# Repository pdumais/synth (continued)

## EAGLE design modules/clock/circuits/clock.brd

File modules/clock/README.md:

# Clock module
A rotary encoder connected to the module will set the clock to a BPM from 30 to 240. 
1 square wave output on the CLK pin, and another one, 8 times faster, on the clk8 output.

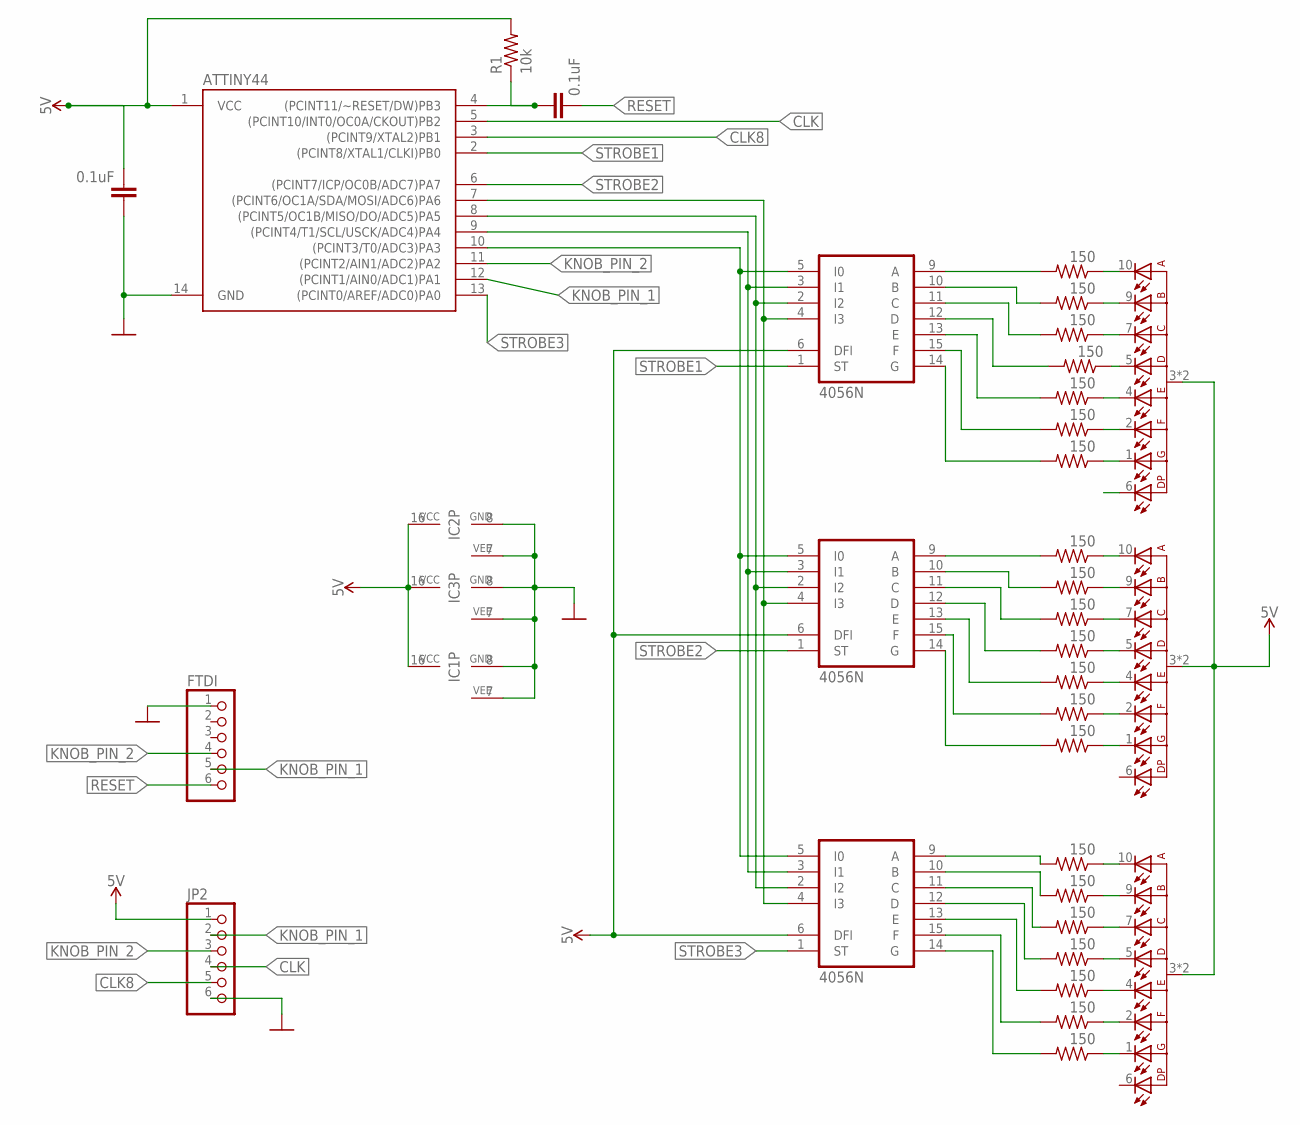
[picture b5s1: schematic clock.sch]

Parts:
ATTINY44: ATTINY84ATTINY84-20PU; DIP14
C2, C3: 0.1uF; CAP-PTH-SMALL-KIT
D1, D2, D3: 157119S12801; WL-T7DS_0.39INCH
FTDI: PINHD-1X6; 1X06
IC1, IC2, IC3: 4056N; DIL16
JP2: PINHD-1X6; 1X06
R1: 10k; 0207/12
R2, R3, R4, R5, R6, R7, R8, R10, R11, R12, R13, R14, R15, R16, R18, R19, R20, R21, R22, R23, R24: 150; 0207/12

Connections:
5V: ATTINY44.1 (VCC), C3.2, D1.3 (+), D1.8 (+), D2.3 (+), D2.8 (+), D3.3 (+), D3.8 (+), IC1.6 (DFI), IC1.16 (VCC), IC2.6 (DFI), IC2.16 (VCC), IC3.6 (DFI), IC3.16 (VCC), JP2.1, R1.2
CLK: ATTINY44.5 ((PCINT10/INT0/OC0A/CKOUT)PB2), JP2.4
CLK8: ATTINY44.3 ((PCINT9/XTAL2)PB1), JP2.5
GND: ATTINY44.14 (GND), C3.1, FTDI.1, IC1.7 (VEE), IC1.8 (GND), IC2.7 (VEE), IC2.8 (GND), IC3.7 (VEE), IC3.8 (GND), JP2.6
KNOB_PIN_1: ATTINY44.12 ((PCINT1/AIN0/ADC1)PA1), FTDI.5, JP2.2
KNOB_PIN_2: ATTINY44.11 ((PCINT2/AIN1/ADC2)PA2), FTDI.4, JP2.3
unnamed: IC1.9 (A), R18.2
unnamed: ATTINY44.4 ((PCINT11/~RESET/DW)PB3), C2.1, R1.1
unnamed: ATTINY44.10 ((PCINT3/T0/ADC3)PA3), IC1.5 (I0), IC2.5 (I0), IC3.5 (I0)
unnamed: IC1.10 (B), R19.2
unnamed: ATTINY44.9 ((PCINT4/T1/SCL/USCK/ADC4)PA4), IC1.3 (I1), IC2.3 (I1), IC3.3 (I1)
unnamed: ATTINY44.8 ((PCINT5/OC1B/MISO/DO/ADC5)PA5), IC1.2 (I2), IC2.2 (I2), IC3.2 (I2)
unnamed: ATTINY44.7 ((PCINT6/OC1A/SDA/MOSI/ADC6)PA6), IC1.4 (I3), IC2.4 (I3), IC3.4 (I3)
unnamed: IC1.11 (C), R20.2
unnamed: IC1.12 (D), R21.2
unnamed: IC1.13 (E), R22.2
unnamed: IC1.15 (F), R23.2
unnamed: IC1.14 (G), R24.2
unnamed: IC3.14 (G), R16.2
unnamed: IC3.15 (F), R15.2
unnamed: IC3.13 (E), R14.2
unnamed: IC3.12 (D), R13.2
unnamed: IC3.11 (C), R12.2
unnamed: IC3.10 (B), R11.2
unnamed: IC3.9 (A), R10.2
unnamed: IC2.14 (G), R8.2
unnamed: IC2.15 (F), R7.2
unnamed: IC2.13 (E), R6.2
unnamed: IC2.12 (D), R5.2
unnamed: IC2.11 (C), R4.2
unnamed: IC2.10 (B), R3.2
unnamed: IC2.9 (A), R2.2
unnamed: D1.10 (7), R2.1
unnamed: D1.9 (6), R3.1
unnamed: D1.7 (4), R4.1
unnamed: D1.5 (2), R5.1
unnamed: D1.4 (1), R6.1
unnamed: D1.2 (9), R7.1
unnamed: D1.1 (10), R8.1
unnamed: D3.10 (7), R10.1
unnamed: D3.9 (6), R11.1
unnamed: D3.7 (4), R12.1
unnamed: D3.5 (2), R13.1
unnamed: D3.4 (1), R14.1
unnamed: D3.2 (9), R15.1
unnamed: D3.1 (10), R16.1
unnamed: D2.10 (7), R18.1
unnamed: D2.9 (6), R19.1
unnamed: D2.7 (4), R20.1
unnamed: D2.5 (2), R21.1
unnamed: D2.4 (1), R22.1
unnamed: D2.2 (9), R23.1
unnamed: D2.1 (10), R24.1
RESET: C2.2, FTDI.6
STROBE1: ATTINY44.2 ((PCINT8/XTAL1/CLKI)PB0), IC2.1 (ST)
STROBE2: ATTINY44.6 ((PCINT7/ICP/OC0B/ADC7)PA7), IC3.1 (ST)
STROBE3: ATTINY44.13 ((PCINT0/AREF/ADC0)PA0), IC1.1 (ST)

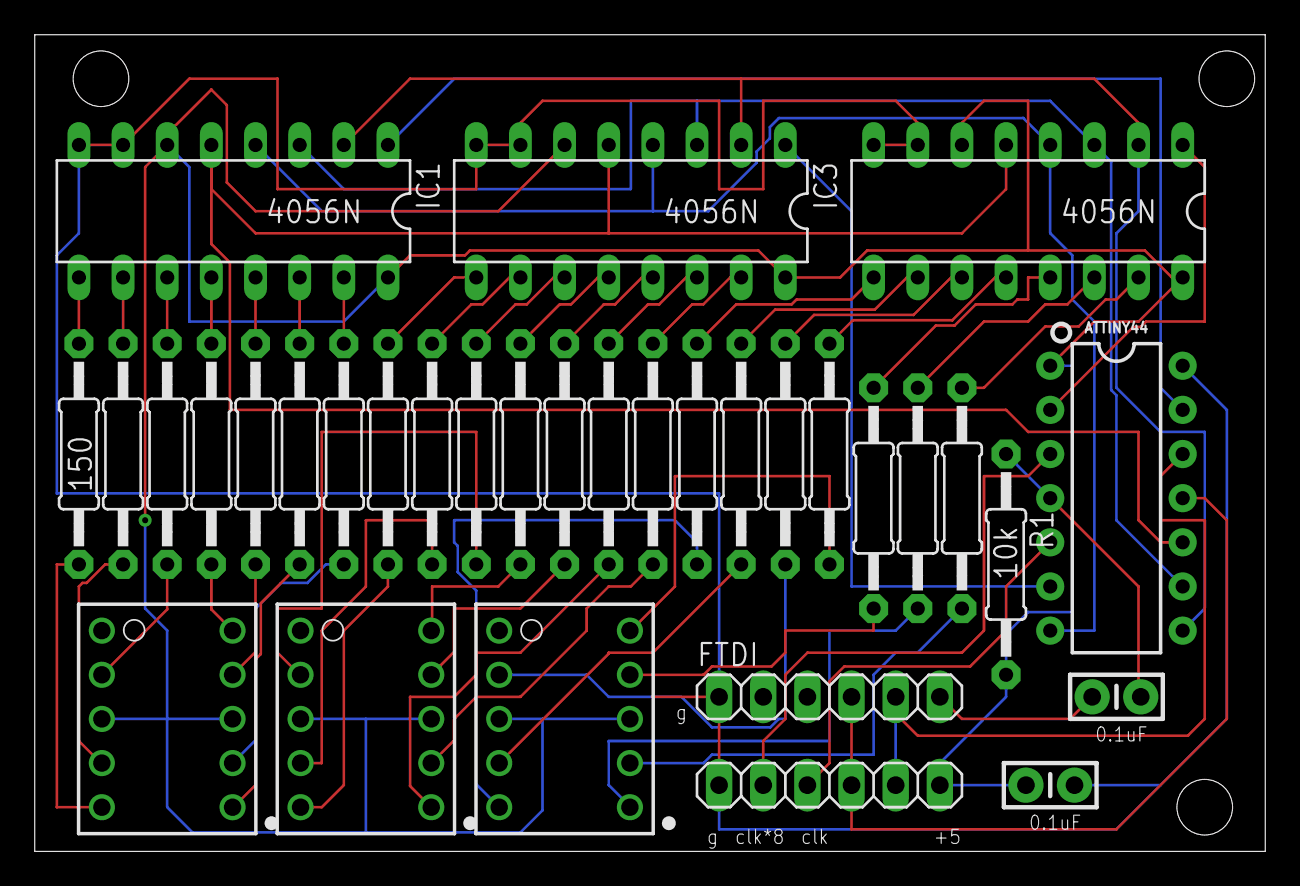
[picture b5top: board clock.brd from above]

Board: 2 copper layers, 70.8 x 47.0 mm, 33 parts (0 on the bottom side), 57 nets.

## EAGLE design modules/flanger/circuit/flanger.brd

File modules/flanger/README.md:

# Flanger
Based on a 2048 stage BBD.

# Design
```mermaid
graph LR;
    Input-->InputMixer;
    InputMixer-->OutputMixer;
    InputMixer-->InLPF;
    InLPF-->BBD;
    BBD-->OutLPF;
    OutLPF-->OutputMixer;  
    OutLPF-->InputMixer;
```

# Inputs
    Analog controls
        Audio In
        LFO CV: input CV to use as external LFO. Will be ignored unless Rate and Depth are both zero
        Dry/Wet: output Mixer
        trimpot: for the BBD outputs balancing

    uC controls
        Rate: To control the speed of the embeded (in the uC) triangle LFO
        Depth: To control the amplitude of the LFO. 
        Offset: Base value on which the LFO will be added 

# Outputs
    Audio Out

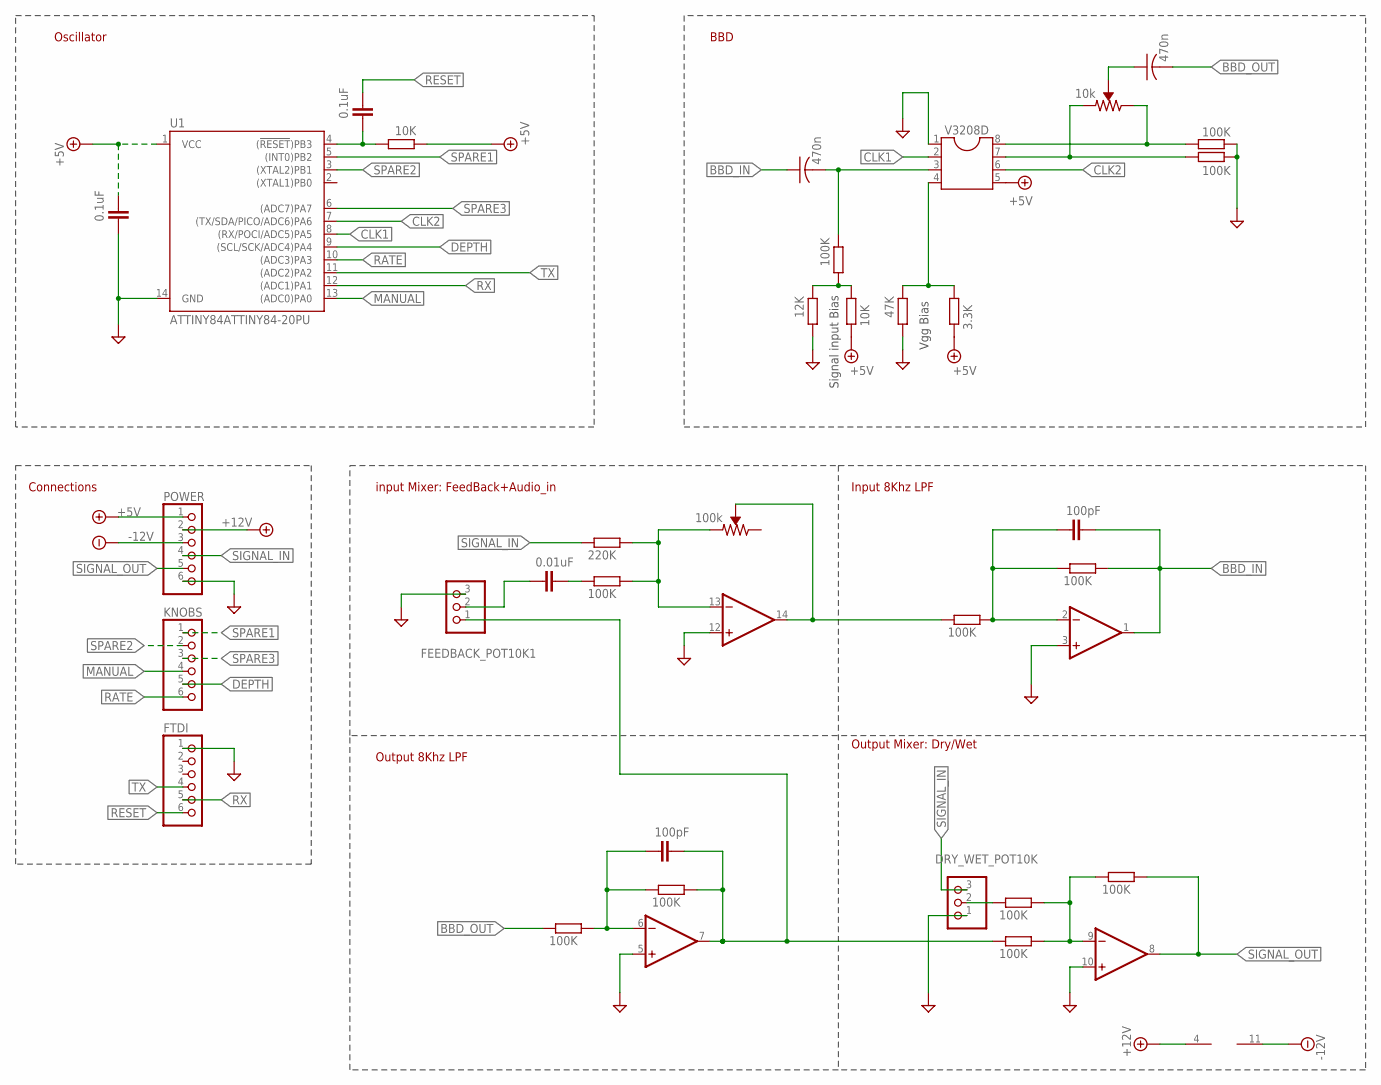
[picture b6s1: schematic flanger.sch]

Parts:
C1, C2: 470n; C050-025X075
C3, C4: 100pF; C5B2.5
C5: 0.01uF; C5B2.5
C6, C7: 0.1uF; C5B2.5
DRY_WET_POT10K: PINHD-1X3; 1X03
FEEDBACK_POT10K1: PINHD-1X3; 1X03
FTDI: PINHD-1X6; 1X06
IC1: LM324N; DIL14
KNOBS: PINHD-1X6; 1X06
POWER: PINHD-1X6; 1X06
R1: 12K; 0207/10
R2, R6, R7, R8, R9, R10, R11, R13, R14, R16, R17: 100K; 0207/10
R3, R18: 10K; 0207/10
R4: 47K; 0207/10
R5: 3.3K; 0207/10
R15: 220K; 0207/10
U1: ATTINY84ATTINY84-20PU; DIP14
V3208D: DIL8; DIL08
VR1: 10k; TRIMPOT-PTH-3386U
VR2: 100k; TRIMPOT-PTH-3386U

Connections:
+5V: C6.2, POWER.1, R3.2, R5.2, R18.2, U1.1 (VCC), V3208D.5
+12V: IC1.4 (V+), POWER.2
-12V: IC1.11 (V-), POWER.3
BBD_IN: C1.1, C3.2, IC1.1 (OUT), R8.2
BBD_OUT: C2.2, R11.1
CLK1: U1.8 ((RX/POCI/ADC5)PA5), V3208D.2
CLK2: U1.7 ((TX/SDA/PICO/ADC6)PA6), V3208D.6
DEPTH: KNOBS.5, U1.9 ((SCL/SCK/ADC4)PA4)
GND: C6.1, DRY_WET_POT10K.1, FEEDBACK_POT10K1.3, FTDI.1, IC1.3 (+IN), IC1.5 (+IN), IC1.10 (+IN), IC1.12 (+IN), POWER.6, R1.1, R4.1, R6.1, R7.1, U1.14 (GND), V3208D.1
MANUAL: KNOBS.4, U1.13 ((ADC0)PA0)
unnamed: R6.2, V3208D.8, VR1.3 (CW)
unnamed: R7.2, V3208D.7, VR1.1 (CCW)
unnamed: C1.2, R2.2, V3208D.3
unnamed: C2.1, VR1.2 (WIPER)
unnamed: R1.2, R2.1, R3.1
unnamed: R4.2, R5.1, V3208D.4
unnamed: IC1.13 (-IN), R15.2, R16.2, VR2.1 (CCW)
unnamed: C3.1, IC1.2 (-IN), R8.1, R9.2
unnamed: C4.1, IC1.6 (-IN), R10.1, R11.2
unnamed: DRY_WET_POT10K.2, R17.1
unnamed: IC1.14 (OUT), R9.1, VR2.2 (WIPER)
unnamed: C4.2, FEEDBACK_POT10K1.1, IC1.7 (OUT), R10.2, R14.1
unnamed: IC1.9 (-IN), R13.1, R14.2, R17.2
unnamed: C5.2, R16.1
unnamed: C5.1, FEEDBACK_POT10K1.2
unnamed: C7.1, R18.1, U1.4 ((!RESET!)PB3)
RATE: KNOBS.6, U1.10 ((ADC3)PA3)
RESET: C7.2, FTDI.6
RX: FTDI.5, U1.12 ((ADC1)PA1)
SIGNAL_IN: DRY_WET_POT10K.3, POWER.4, R15.1
SIGNAL_OUT: IC1.8 (OUT), POWER.5, R13.2
SPARE1: KNOBS.1, U1.5 ((INT0)PB2)
SPARE2: KNOBS.2, U1.3 ((XTAL2)PB1)
SPARE3: KNOBS.3, U1.6 ((ADC7)PA7)
TX: FTDI.4, U1.11 ((ADC2)PA2)

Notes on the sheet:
Vgg Bias
Signal input Bias
Input 8Khz LPF
Output 8Khz LPF
Output Mixer: Dry/Wet
input Mixer: FeedBack+Audio_in
BBD
Oscillator
Connections

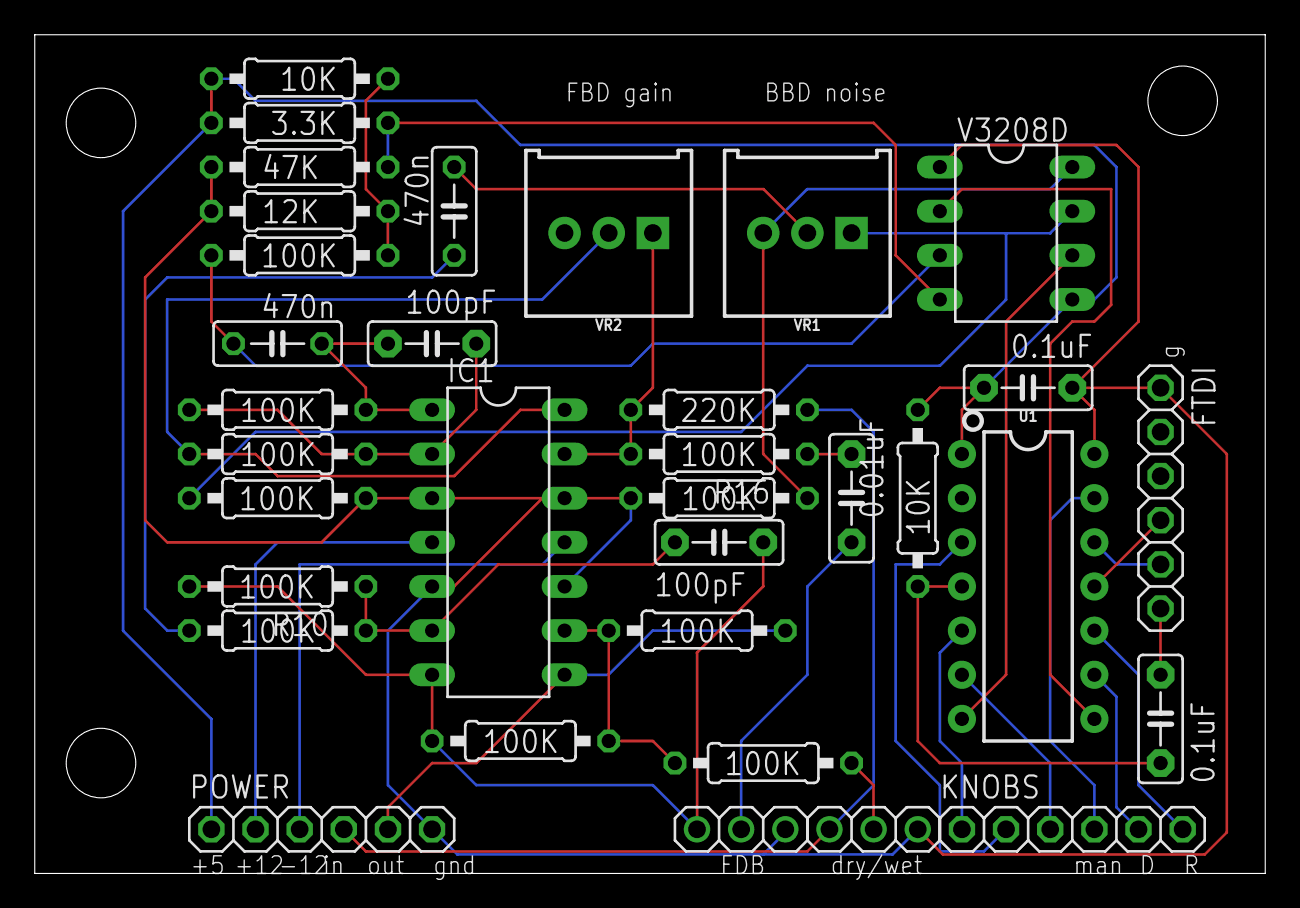
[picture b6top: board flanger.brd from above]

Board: 2 copper layers, 70.8 x 48.2 mm, 34 parts (0 on the bottom side), 35 nets.

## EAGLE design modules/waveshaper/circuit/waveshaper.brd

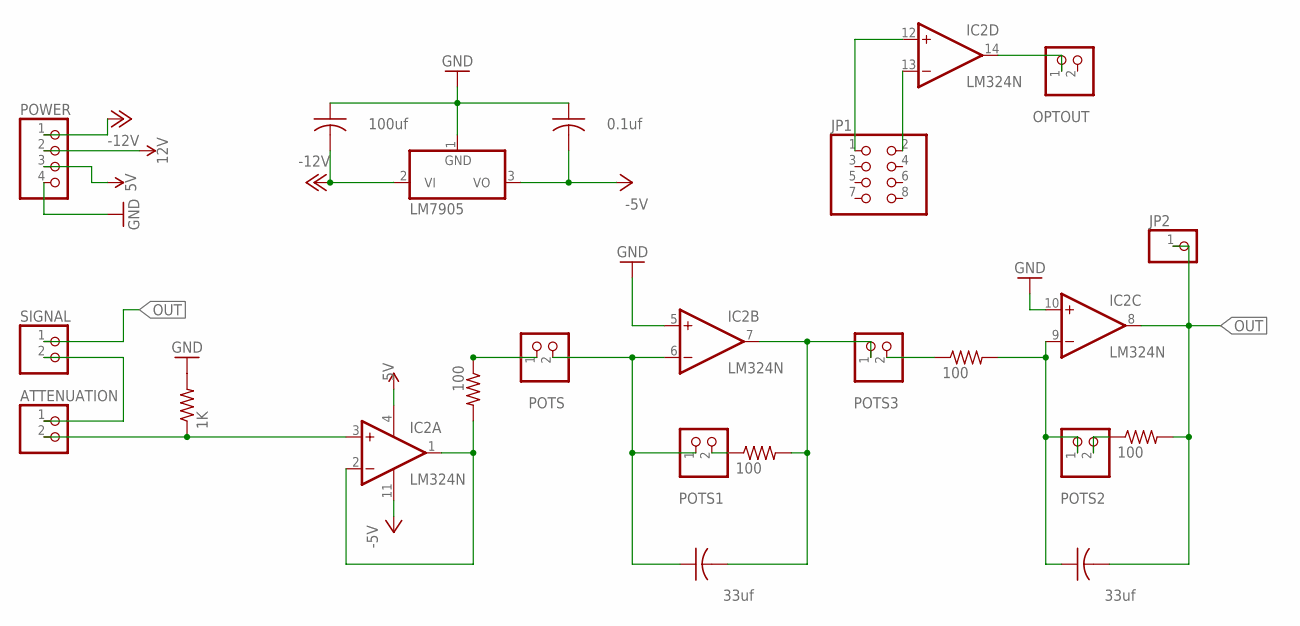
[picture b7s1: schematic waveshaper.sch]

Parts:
ATTENUATION: PINHD-1X2; 1X02
C1: 100uf; C025-024X044
C2: 0.1uf; C025-024X044
C3, C4: 33uf; C025-024X044
IC2: LM324N; DIL14
JP1: PINHD-2X4; 2X04
JP2: PINHD-1X1; 1X01
LM7905: 7905T; TO220H
OPTOUT: PINHD-1X2; 1X02
POTS, POTS1, POTS2, POTS3: PINHD-1X2; 1X02
POWER: PINHD-1X4; 1X04
R1: 1K; 0207/12
R2, R3, R4, R5: 100; 0207/12
SIGNAL: PINHD-1X2; 1X02

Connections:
5V: IC2.4 (V+), POWER.3
12V: POWER.2
-5V: C2.2, IC2.11 (V-), LM7905.3 (VO)
-12V: C1.2, LM7905.2 (VI), POWER.1
GND: C1.1, C2.1, IC2.5 (+IN), IC2.10 (+IN), LM7905.1 (GND), POWER.4, R1.2
IN: ATTENUATION.2, IC2.3 (+IN), R1.1
unnamed: ATTENUATION.1, SIGNAL.2
unnamed: C3.1, IC2.6 (-IN), POTS.2, POTS1.1
unnamed: C3.2, IC2.7 (OUT), POTS3.1, R3.2
unnamed: C4.1, IC2.9 (-IN), POTS2.1, R5.2
unnamed: IC2.14 (OUT), OPTOUT.1
unnamed: IC2.13 (-IN), JP1.2
unnamed: IC2.12 (+IN), JP1.1
unnamed: IC2.1 (OUT), IC2.2 (-IN), R2.2
unnamed: POTS.1, R2.1
unnamed: POTS1.2, R3.1
unnamed: POTS2.2, R4.1
unnamed: POTS3.2, R5.1
OUT: C4.2, IC2.8 (OUT), JP2.1, R4.2, SIGNAL.1

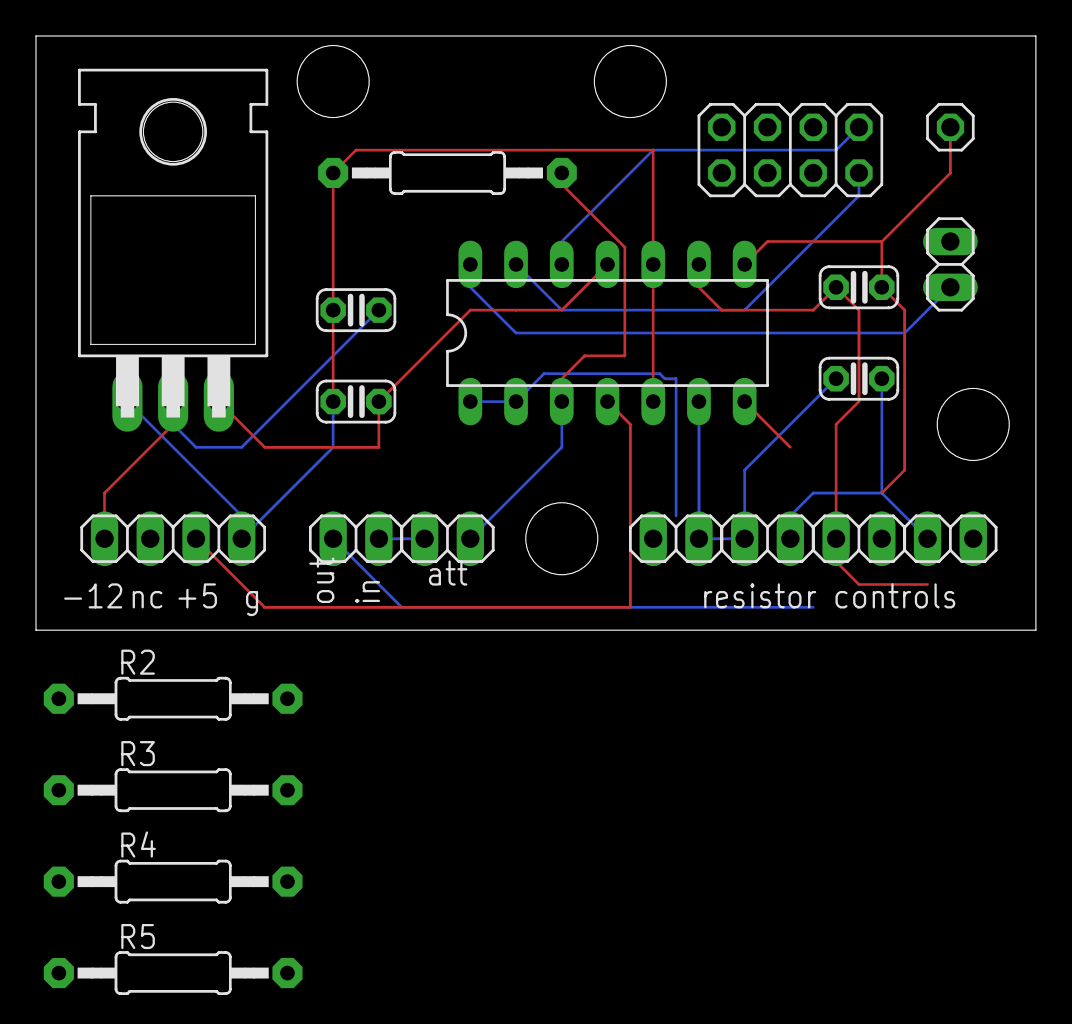
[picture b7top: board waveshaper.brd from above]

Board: 2 copper layers, 55.5 x 33.0 mm, 21 parts (0 on the bottom side), 18 nets.

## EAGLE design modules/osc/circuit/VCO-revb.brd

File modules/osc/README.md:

# Oscillator
- 2 square wave oscillators.
    1 osc as main wave, and 2nd osc used as detune.
- 4 sqaurewave LFOs

# Inputs
- VCO freq
- Detune
- VCO pulse width
- LFO1 freq 
- LFO2 freq 
- LFO3 freq 
- LFO4 freq 

# Outputs
- Audio out
- LFO1
- LFO2
- LFO3
- LFO4

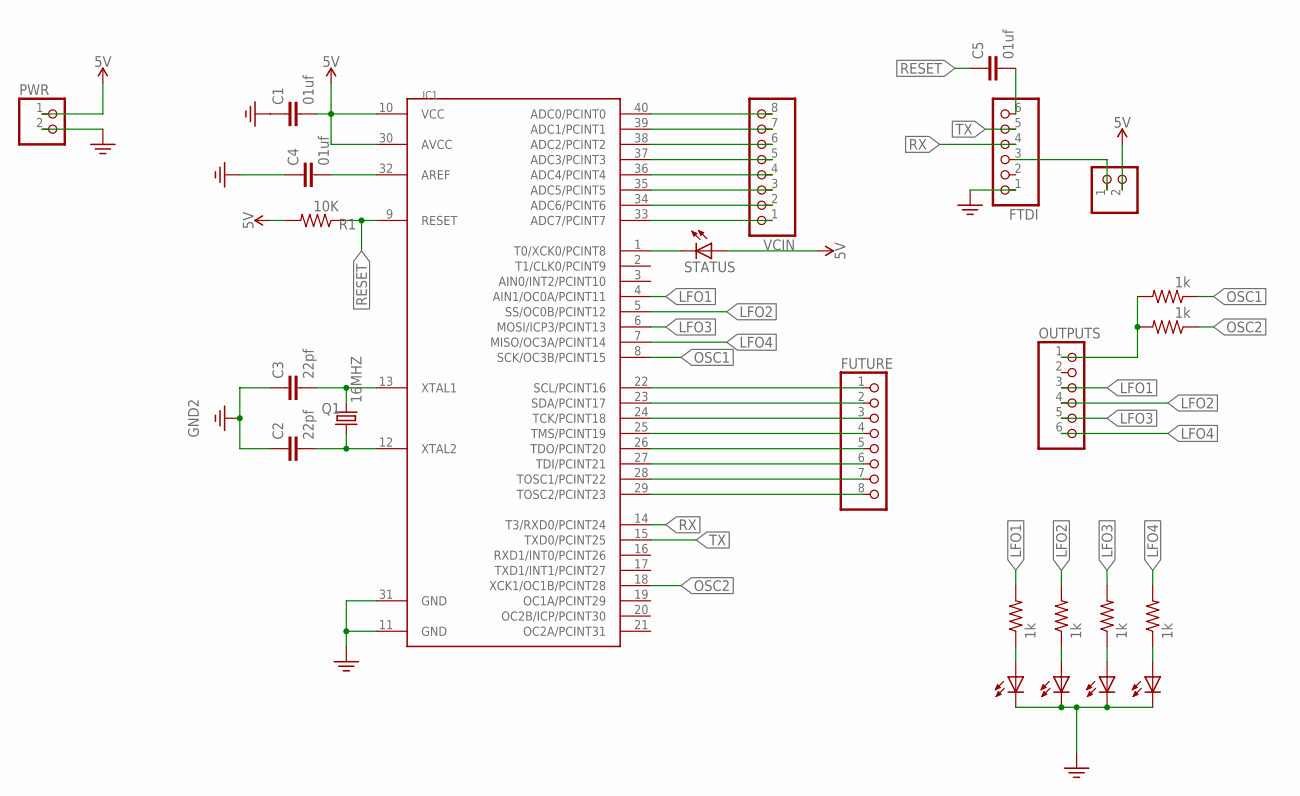
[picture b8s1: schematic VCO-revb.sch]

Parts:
C1, C4, C5: 01uf; C025-024X044
C2, C3: 22pf; C025-024X044
FTDI: PINHD-1X6; 1X06
FUTURE: PINHD-1X8BIG; 1X08-BIG
IC1: MEGA1284P; DIL40
LFO1, LFO2, LFO3, LFO4: LED5MM
OUTPUTS: PINHD-1X6; 1X06
PWR, PWR1: PINHD-1X2; 1X02
Q1: 16MHZ; HC49/S
R1: 10K; 0207/12
R2, R3, R4, R5, R6, R7: 1k; 0207/12
STATUS: LED5MM
VCIN: PINHD-1X8; 1X08

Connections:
3.3V: C1.1, C2.1, C3.1, C4.1, FTDI.1, IC1.11 (GND), IC1.31 (GND), LFO1.K (C), LFO2.K (C), LFO3.K (C), LFO4.K (C), PWR.2
LFO1: IC1.4 (AIN1/OC0A/PCINT11), OUTPUTS.3, R4.2
LFO2: IC1.5 (SS/OC0B/PCINT12), OUTPUTS.4, R3.2
LFO3: IC1.6 (MOSI/ICP3/PCINT13), OUTPUTS.5, R2.2
LFO4: IC1.7 (MISO/OC3A/PCINT14), OUTPUTS.6, R5.2
unnamed: LFO1.A, R4.1
unnamed: IC1.40 (ADC0/PCINT0), VCIN.8
unnamed: IC1.39 (ADC1/PCINT1), VCIN.7
unnamed: IC1.38 (ADC2/PCINT2), VCIN.6
unnamed: IC1.37 (ADC3/PCINT3), VCIN.5
unnamed: IC1.36 (ADC4/PCINT4), VCIN.4
unnamed: IC1.35 (ADC5/PCINT5), VCIN.3
unnamed: IC1.34 (ADC6/PCINT6), VCIN.2
unnamed: IC1.33 (ADC7/PCINT7), VCIN.1
unnamed: C3.2, IC1.13 (XTAL1), Q1.2
unnamed: C2.2, IC1.12 (XTAL2), Q1.1
unnamed: LFO2.A, R3.1
unnamed: C4.2, IC1.32 (AREF)
unnamed: C5.2, FTDI.6
unnamed: LFO3.A, R2.1
unnamed: LFO4.A, R5.1
unnamed: OUTPUTS.1, R6.2, R7.2
unnamed: FUTURE.1, IC1.22 (SCL/PCINT16)
unnamed: FUTURE.2, IC1.23 (SDA/PCINT17)
unnamed: FUTURE.3, IC1.24 (TCK/PCINT18)
unnamed: FUTURE.4, IC1.25 (TMS/PCINT19)
unnamed: FUTURE.5, IC1.26 (TDO/PCINT20)
unnamed: FTDI.3, PWR1.1
unnamed: IC1.1 (T0/XCK0/PCINT8), STATUS.K (C)
unnamed: FUTURE.6, IC1.27 (TDI/PCINT21)
unnamed: FUTURE.7, IC1.28 (TOSC1/PCINT22)
unnamed: FUTURE.8, IC1.29 (TOSC2/PCINT23)
OSC1: IC1.8 (SCK/OC3B/PCINT15), R6.1
OSC2: IC1.18 (XCK1/OC1B/PCINT28), R7.1
RESET: C5.1, IC1.9 (RESET), R1.1
RX: FTDI.4, IC1.14 (T3/RXD0/PCINT24)
TX: FTDI.5, IC1.15 (TXD0/PCINT25)
VDD: C1.2, IC1.10 (VCC), IC1.30 (AVCC), PWR.1, PWR1.2, R1.2, STATUS.A

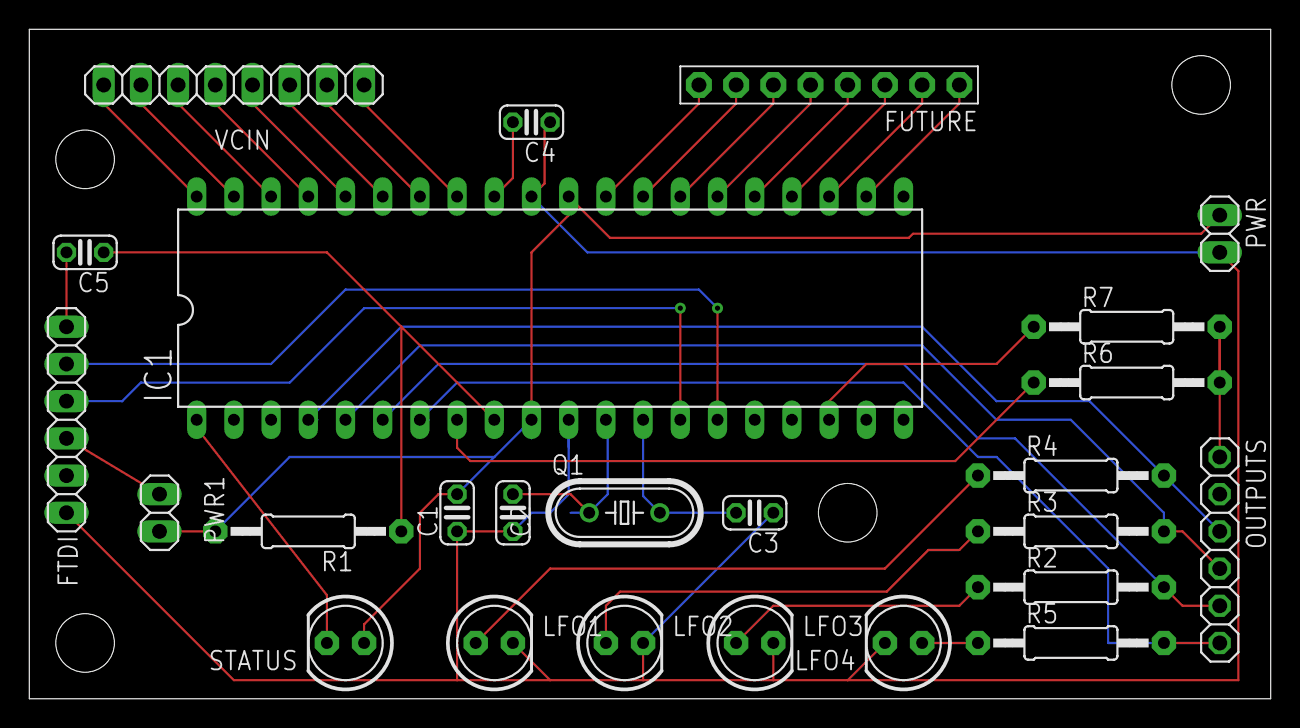
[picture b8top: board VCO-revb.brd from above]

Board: 2 copper layers, 84.8 x 45.7 mm, 25 parts (0 on the bottom side), 38 nets.

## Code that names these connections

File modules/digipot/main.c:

#define F_CPU            8000000UL

#include <avr/io.h>
#include <avr/interrupt.h>
#include <avr/sleep.h>

#define LED_OFF_TIME     300000L
#define LED_ON_TIME      2000L

uint8_t current_adc;

void adc_init() {
    ADMUX = (0 << REFS0) | 0b111; // AVcc with capacitor to ARef
    ADCSRB |= (1 << ADLAR);
    ADCSRA |= (1 << ADPS0) | (1 << ADPS2) | (1 << ADPS1) | (1 << ADEN) | (1<<ADSC);
} 

uint8_t adc_read() {
    if (!(ADCSRA & (1 << ADIF))) return current_adc;

    uint8_t l = ADCL;
    uint8_t h = ADCH;
    ADCSRA |= (1 << ADIF) | (1<<ADSC); // Clear ADIF by writing 1 in it, and start a new conversion
    return h;
}

uint8_t spi_write(uint8_t c) {
    USIDR = c;
    USISR=(1<<USIOIF);  // Clear overflow flag by writing 1 to it.   
    while(1) {
        USICR=(1<<USIWM0)|(1<<USICS1)|(1<<USICLK)|(1<<USITC);
        if ((USISR & (1<<USIOIF)) != 0) break;
    }
    uint8_t ret = USIDR;
    return ret;
}

void digipot_write(uint8_t v) {
    PORTB&=~(1<<PB2);
    spi_write(0);
    spi_write(v);
    PORTB|=(1<<PB2);
}

int main(void)
{
    PORTA=0;
    PORTB=0b101;
    DDRA=(1<<PA5)|(1<<PA4);  
    DDRB=(1 << PB0) | (1 <<PB2);

    adc_init();

    digipot_write(255);

    uint32_t led_flash = 0;
    uint8_t current_adc = 0;
    uint8_t tmp = 0;
    while (1) {
        tmp = adc_read();
        if (tmp != current_adc) {
            current_adc = tmp;
        }

        if (current_adc <200) PORTB|=1; else PORTB &=0xFE;
 /*       led_flash++;
        if (led_flash == LED_OFF_TIME) PORTB&=0xFE; 
        if (led_flash == (LED_ON_TIME+LED_OFF_TIME)) {
            led_flash = 0;
            PORTB|=0x1; 
        }*/

    digipot_write(current_adc);
//    digipot_write(30);

//    PORTB&=~(1<<PB2);
//    spi_write(0);
//    spi_write(64);
//    PORTB|=(1<<PB2);
//        PORTB&=~(0b10);
//        spi_write(0);
//        spi_write(255);
//        PORTB|=0b10;

    }
}

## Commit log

2022-01-30 initial
2022-01-30 circuits
2022-01-30 circuits changes
2022-02-02 Cleanup
2022-02-02 Adding circuits
2022-02-02 digipots CV
2022-02-03 sequencer design
2022-02-03 Sync
2022-02-04 divider
2022-02-04 personal notes
2022-02-04 updating readme
2022-02-04 updating notes
2022-02-05 Sequencer design complete
2022-02-06 adding clock module
2022-02-06 Notes
2022-02-08 PCB correction for clock
2022-02-08 adding noisegen design
2022-02-08 Clock code
2022-02-10 Seq board
2022-02-11 Adding counter to seq
2022-02-11 vcf and vca info
2022-02-12 VCA design
2022-02-12 midi2cv
2022-02-12 Resistor changes for vca
2022-02-13 schematic for midi2cv
2022-02-13 midi2cv code
2022-02-14 midi2cv board
2022-02-15 sequencer board
2022-02-16 unipolar2bipolar
2022-02-16 uni2bi
2022-02-18 adsr board
2022-02-18 adsr and drum
2022-02-18 adsr
2022-02-21 Adding doc
2022-02-21 vca changes
2022-02-21 modified VCA
2022-02-21 vco rev b
2022-02-21 Finished VCA
2022-02-21 adsr works
2022-02-23 Adding VCF circuit
2022-02-26 vcf done
2022-02-27 Adding resistors before each pots on wavshapper to avoid shorting when pot is at 0%
2022-03-05 Flanger
2022-03-10 Sequencer fixes
2022-03-16 Noise firmware. ADSR and midi2CV fixes
2022-03-16 Adding bass drum design (alpha)
2022-03-19 Started Drum circuit
2022-04-01 a few misc changes
2022-04-01 Drums
2022-04-05 drum board
2022-04-05 drum board cleanup
2022-04-07 drum machine
2022-04-18 long overdue commit
2022-04-19 software sequencer
2022-04-19 sequencer software
2022-04-25 Lots of new stuff
2022-05-31 Long overdue pending commit
